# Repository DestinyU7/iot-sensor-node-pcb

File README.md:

# IoT Sensor Node — Custom Arduino Shield PCB

A two-layer PCB designed from scratch in KiCad, fabricated at JLCPCB, hand-assembled, and running firmware that publishes live temperature telemetry to a cloud dashboard over Wi-Fi.

## Overview

University of Delaware coursework: **ELEG 298, ECE Design Challenges (Spring 2025)**. My first board taken end to end — schematic capture through layout, design rule check, Gerber generation, fabrication order, assembly, and bring-up.

The board is an Arduino Uno shield carrying a DHT20 temperature/humidity sensor interface, an ESP-01S Wi-Fi module on a UART link, status LEDs, and the supporting passives. Firmware reads temperature, classifies the trend as rising, falling or stable, signals that trend on two LEDs, and publishes each reading to an Adafruit IO feed over Wi-Fi.

<p align="center"><em>Left: the two-layer layout in KiCad. Right: the fabricated board hand-assembled, with the ESP-01S module fitted and a Grove sensor attached.</em></p>

## Hardware

| Function | Part |
|---|---|
| Host | Arduino Uno (shield form factor) |
| Wi-Fi | ESP-01S (ESP8266) over software UART |
| Sensor | DHT20 temperature / humidity (I²C, Grove connector) |
| Indicators | 2 × LED with 1 kΩ current-limiting resistors |
| Power | Bulk 1000 µF electrolytics + 0.1 µF decoupling |
| Level/pull-ups | 1 kΩ / 2 kΩ divider network, 4.7 kΩ I²C pull-ups |

Two copper layers (`F_Cu`, `B_Cu`), silkscreen on both sides, mounting holes, and an ICSP header passthrough.

## Software / Tools

- **KiCad** — schematic capture, PCB layout, DRC, Gerber and drill file export
- **Arduino C++** — `SoftwareSerial`, Grove DHT library
- **JLCPCB** — fabrication
- **Adafruit IO** — cloud feed and dashboard
- DigiKey-sourced BOM with costed line items

## Architecture

```mermaid
flowchart LR
    DHT["DHT20 sensor<br/>temperature + humidity"] -->|I2C| UNO
    UNO["Arduino Uno<br/>trend classifier"] -->|software UART<br/>9600 baud| ESP["ESP-01S<br/>ESP8266 Wi-Fi"]
    UNO --> LEDS["Red / green LEDs<br/>trend indication"]
    ESP -->|Wi-Fi| AIO["Adafruit IO<br/>temperature-feed"]
    AIO --> DASH["Cloud dashboard"]
```

The Uno drives the ESP-01S through a simple text command protocol over software serial (`wifi_ssid=`, `wifi_pass=`, `io_user=`, `io_key=`, `setup_io`, `setup_pubfeed=`, `send_data=`), with per-command timeouts and a hardware reset line to bring the module up cleanly at boot.

## Key Engineering Work

**Full PCB workflow, not just a schematic.** Component placement, two-layer routing with 45° trace angles and no right-angle bends, an 8 mil minimum line/space rule, silkscreen reference designators and polarity markers on both sides, DRC to zero errors and zero airwires, then Gerber + drill export and a fabrication-portal preview check before ordering. The Gerber set that was actually sent to the fab is in `hardware/gerbers/`.

**Designing for hand assembly.** The board mixes through-hole and SMD parts, with part choice and spacing driven by what could realistically be soldered by hand and reworked if wrong — a constraint that shaped the layout as much as the electrical requirements did.

**Trend classification instead of raw reporting.** Firmware compares each reading against the previous one with a ±0.1 °C tolerance band and tracks the last rising value, so the LEDs show direction of change rather than flickering on sensor noise, plus a stable-band indication between 22–24 °C.

**Reset sequencing.** The ESP-01S is held in reset at boot and released deliberately before any command is sent, which avoids the race where configuration commands are transmitted before the module's UART is listening.

## Testing / Validation

- **DRC and airwire check** in KiCad before Gerber export; fabrication-portal preview reviewed against the intended layout.
- **Continuity and power-rail checks** on the bare board before any active parts were fitted.
- **Incremental bring-up** — power, then LEDs, then sensor over I²C, then the ESP-01S link, then cloud publishing.
- **End-to-end verification** by watching readings appear on the Adafruit IO dashboard while warming the sensor by hand and confirming the LED trend indication matched.

## Repository Structure

```
firmware/           iot_sensor_node.ino - Arduino firmware
hardware/
  kicad/            schematic and two-layer board layout
  gerbers/          fabrication set sent to JLCPCB (copper, mask, silk, paste, drill)
docs/               final project design report
media/              layout render and photo of the assembled board
```

## Security Note

The Adafruit IO key and Wi-Fi credentials are **redacted** from the committed firmware (`IO_KEY = "REPLACE_WITH_ADAFRUIT_IO_KEY"`). Supply your own credentials to run it. No live key appears anywhere in this repository or its commit history.

## What I Learned

The layout was where the real learning was. A schematic that passes electrical rules can still be a board that is painful to assemble, hard to probe, and awkward to mount — trace angles, part spacing, silkscreen legibility and test-point access are decisions you only appreciate once you are holding the fabricated board with an iron in your hand.

Ordering it was the other half. Once Gerbers are submitted there is no undo, which forces a much more careful review pass than any purely simulated assignment ever did.

## Academic Context

University of Delaware, ELEG 298 — ECE Design Challenges, Spring 2025. Design, layout, firmware and assembly are my own work.

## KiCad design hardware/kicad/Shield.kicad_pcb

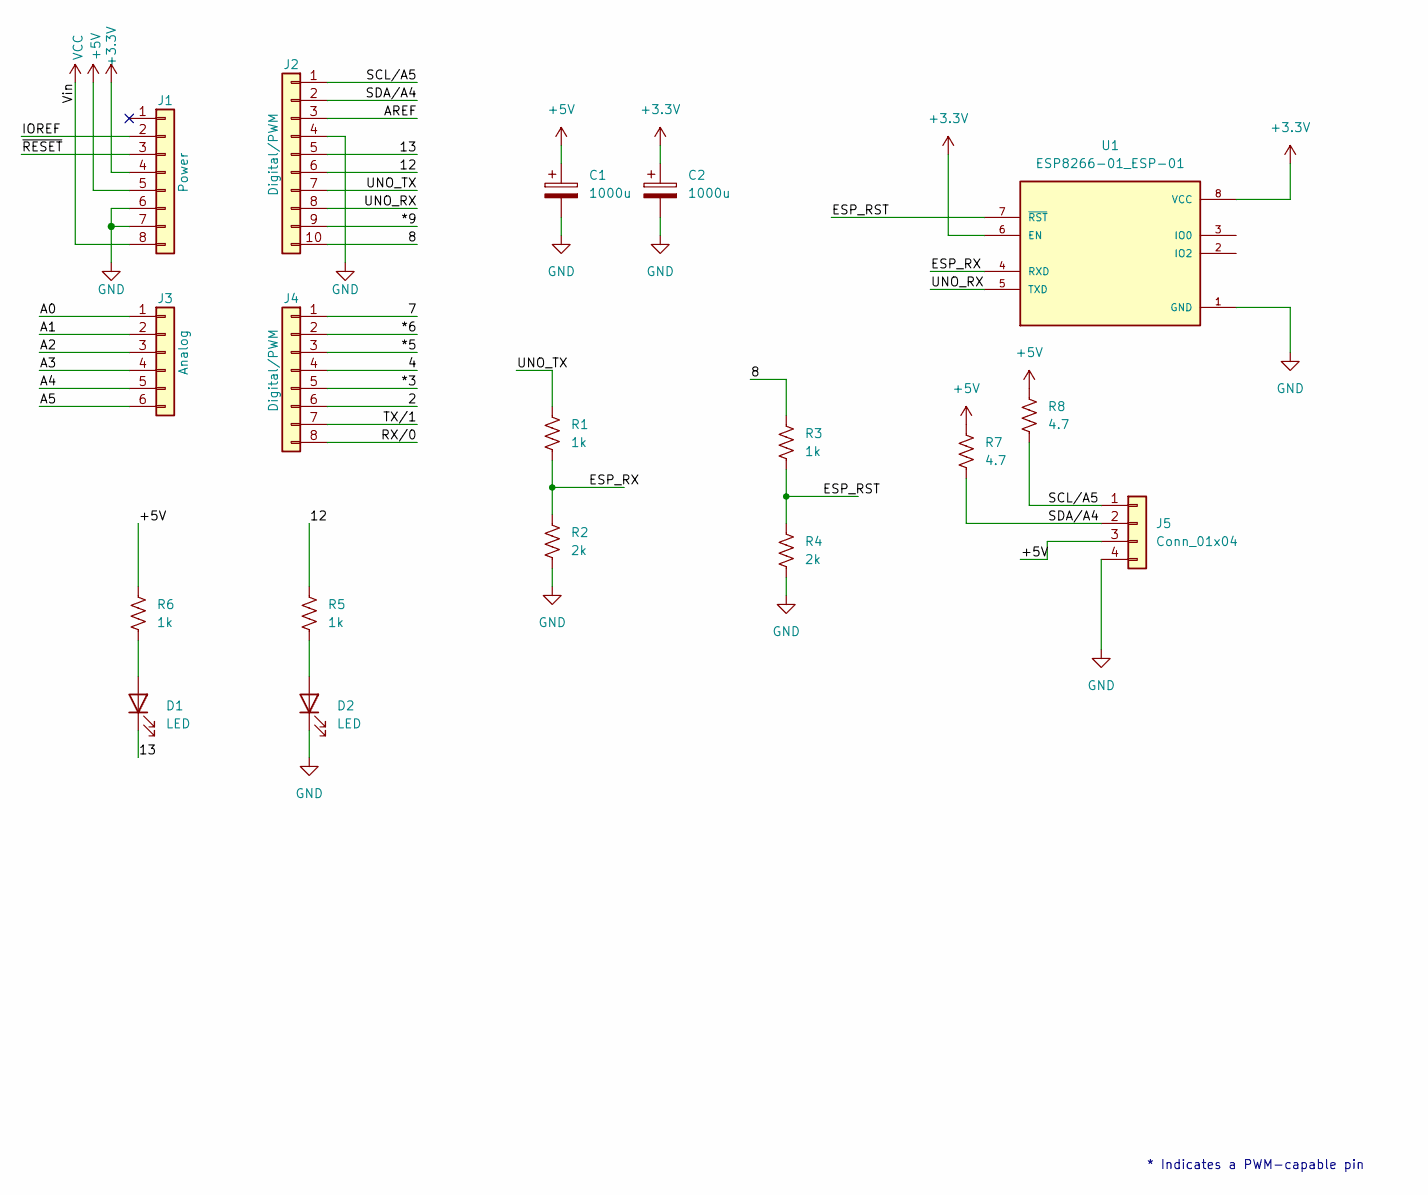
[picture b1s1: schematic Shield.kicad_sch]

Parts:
C1, C2: 1000u; CP_Radial_D10.0mm_P5.00mm
D1, D2: LED; LED_D5.0mm
J1: Power; PinSocket_1x08_P2.54mm_Vertical
J2: Digital/PWM; PinSocket_1x10_P2.54mm_Vertical
J3: Analog; PinSocket_1x06_P2.54mm_Vertical
J4: Digital/PWM; PinSocket_1x08_P2.54mm_Vertical
J5: Conn_01x04; NS-Tech_Grove_1x04_P2mm_Vertical
R1, R3, R5, R6: 1k; R_Axial_DIN0207_L6.3mm_D2.5mm_P10.16mm_Horizontal
R2, R4: 2k; R_Axial_DIN0207_L6.3mm_D2.5mm_P10.16mm_Horizontal
R7, R8: 4.7; R_Axial_DIN0207_L6.3mm_D2.5mm_P10.16mm_Horizontal
U1: ESP8266-01_ESP-01; XCVR_ESP8266-01_ESP-01; PARTREV V1.2

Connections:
+3.3V: C2.1, J1.4, U1.6 (EN), U1.8 (VCC)
+5V: C1.1, J1.5, J5.3, R6.1, R7.1, R8.1; also elsewhere on the board
/2: J4.6
/4: J4.4
/7: J4.1
/8: J2.10, R3.1
/12: J2.6, R5.1
/13: D1.1 (K), J2.5
/*3: J4.5
/*5: J4.3
/*6: J4.2
/*9: J2.9
/A0: J3.1
/A1: J3.2
/A2: J3.3
/A3: J3.4
/A4: J3.5
/A5: J3.6
/AREF: J2.3
/ESP_RST: R3.2, R4.1, U1.7 (~RST)
/ESP_RX: R1.2, R2.1, U1.4 (RXD)
/IOREF: J1.2
/RX/0: J4.8
/SCL/A5: J2.1, J5.1, R8.2
/SDA/A4: J2.2, J5.2, R7.2
/TX/1: J4.7
/UNO_RX: J2.8, U1.5 (TXD)
/UNO_TX: J2.7, R1.1
/~RESET: J1.3
GND: C1.2, C2.2, D2.1 (K), J1.6, J1.7, J2.4, J5.4, R2.2, R4.2, U1.1 (GND); also elsewhere on the board
unnamed: D1.2 (A), R6.2
unnamed: D2.2 (A), R5.2
VCC: J1.8

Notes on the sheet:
* Indicates a PWM-capable pin

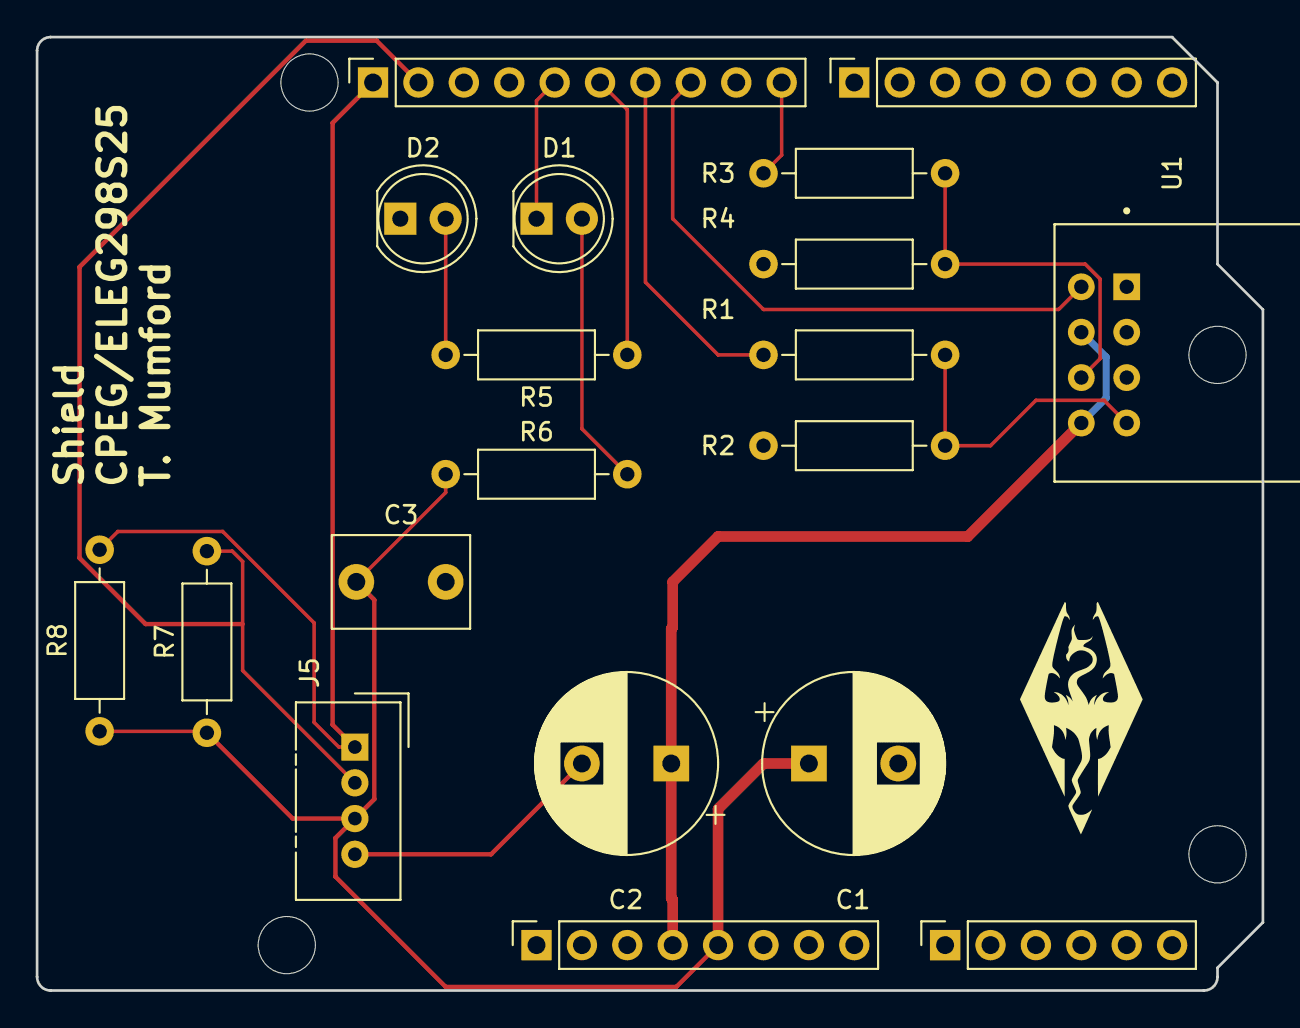
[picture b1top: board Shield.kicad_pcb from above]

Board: 2 copper layers, 68.6 x 53.3 mm, 23 parts (0 on the bottom side), 14 nets.

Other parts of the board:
C3: 0.1u; C_Disc_D7.5mm_W5.0mm_P5.00mm
MH1, MH2, MH3, MH4: MountingHole_3.2mm

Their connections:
+5V: C3.1; also elsewhere on the board
GND: C3.2; also elsewhere on the board
